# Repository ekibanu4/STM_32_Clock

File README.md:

# STM32 Binary Clock Lab

This repository is a development sandbox for a binary clock built around
different STM32 microcontrollers and peripheral combinations. It contains the
current clock firmware, earlier hardware ports, reusable device drivers, board
experiments, KiCad sources, and end-user documentation.

The project is intentionally broader than a single finished product: it is used
to test display concepts, sensors, RTC implementations, power management, alarm
behavior, and small-memory firmware optimizations on real hardware.

## MCU variants

- **STM32L010F4P6** - current primary target and the most complete low-power build.
- **STM32F030F4P6** - compact CubeMX/HAL port used during early hardware tests.
- **STM32F407G-DISC1** - original prototype and development platform.

The default CMake configuration currently builds the STM32L010F4P6 firmware.
Board-specific notes and wiring are kept under [`Core/Src/boards`](Core/Src/boards).

## Hardware and drivers

The repository includes implementations or experiments for:

- a 16-LED binary display driven by chained 74HC595 shift registers;
- a 128x32 OLED display;
- an internal STM32 RTC clocked from a 32.768 kHz LSE crystal;
- the external DS1302 RTC used by earlier board versions;
- AHT10 and DHT11 temperature/humidity sensors;
- BH1750 and analog LDR light sensing with automatic display brightness;
- an ADC resistor ladder for five control buttons;
- active-buzzer alarm output and three persistent alarm slots;
- PIR motion detection, idle display shutdown, battery measurement, and standby
  power handling.

Separate branches also preserve display and peripheral experiments such as the
MAX721x 8x8 LED matrix version.

## Firmware layout

- `Core/Src/app` - clock behavior, alarms, display rendering, environment data,
  automatic modes, and user-interface state.
- `Core/Src/boards` - MCU/board-specific GPIO and peripheral implementations.
- `Core/Src/drivers` - reusable drivers for buttons, buzzer, DHT11, DS1302,
  light sensing, and shift registers.
- `Drivers` - STM32 CMSIS and HAL sources.
- `docs` - user guide, technical reference, diagrams, and promotional assets.
- `Clocl i2C l0 16 -2 595` - KiCad schematic and PCB sources for the current
  STM32L010-based hardware.

## Build

The current target requires CMake, Ninja, and the GNU Arm Embedded toolchain.

```bash
cmake --preset Release
cmake --build --preset Release
```

Debug and Release presets place their output under `build/`.

## Documentation

- [User manual](docs/clock-plus-user-manual.md)
- [Technical reference](docs/clock-plus-technical-reference.md)
- [STM32L010 board notes](Core/Src/boards/l010f4p6/README.md)
- [STM32F030 board notes](Core/Src/boards/f030f4p6/README.md)
- [STM32F407 board notes](Core/Src/boards/f407_disc1/README.md)

This is an experimental hardware/firmware repository. Verify the selected board
configuration, supply voltage, pin mapping, and programming setup before using
it on assembled hardware.

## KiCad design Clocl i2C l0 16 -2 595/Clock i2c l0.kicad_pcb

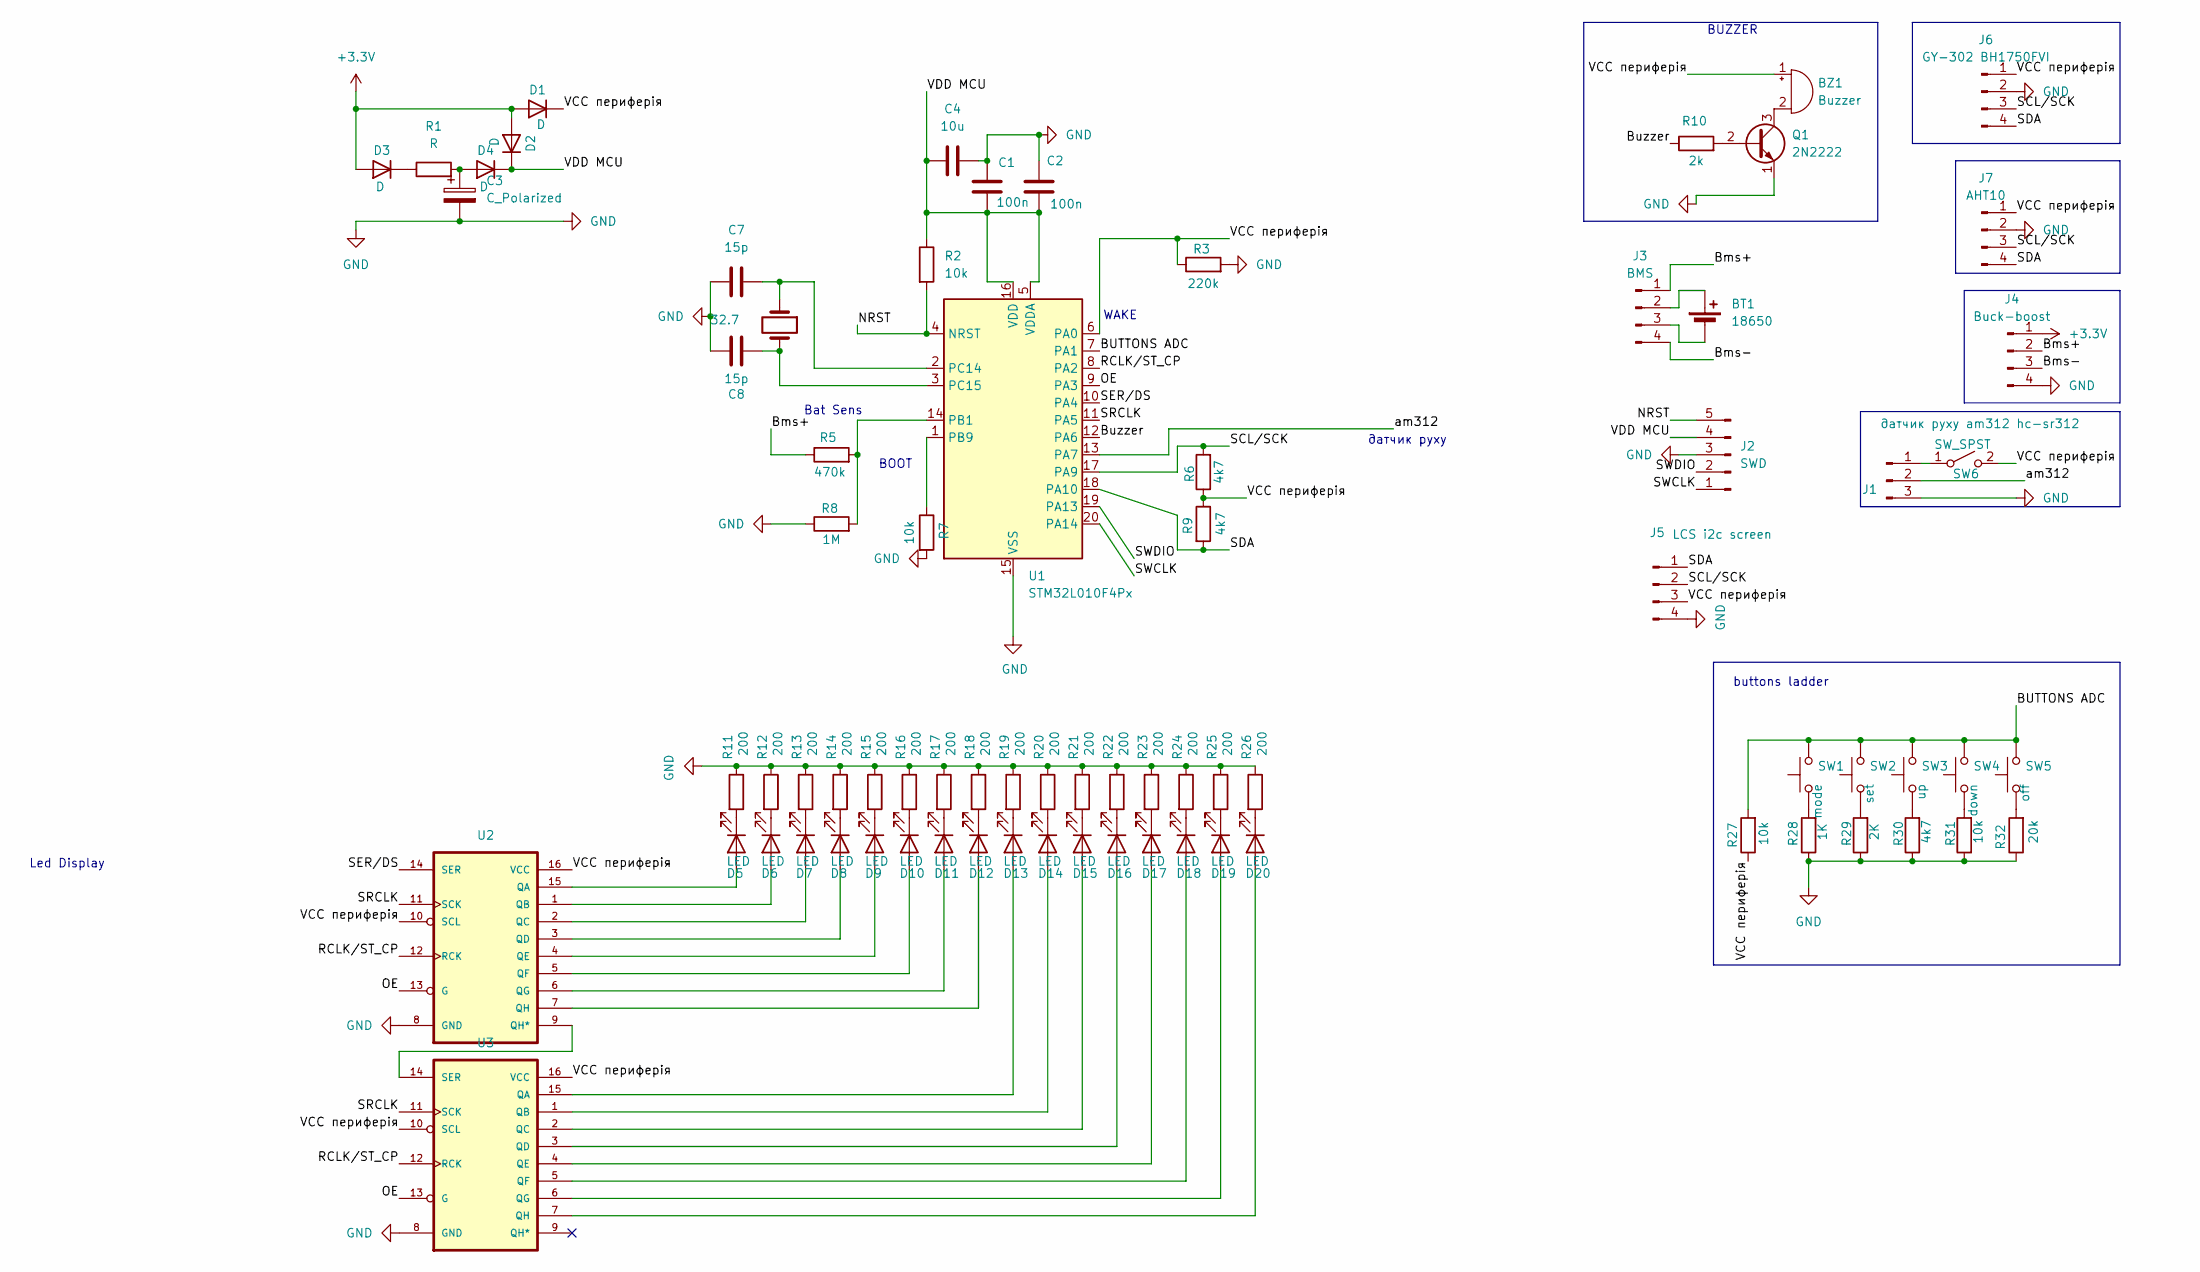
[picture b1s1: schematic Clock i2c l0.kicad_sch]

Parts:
BT1: 18650; BatteryHolder_MPD_BH-18650-PC
BZ1: Buzzer; Buzzer_12x9.5RM7.6
C1, C2: 100n; C_0805_2012Metric_Pad1.18x1.45mm_HandSolder
C3: C_Polarized; CP_Radial_D10.0mm_P5.00mm_P7.50mm
C4: 10u; C_0805_2012Metric_Pad1.18x1.45mm_HandSolder
C7, C8: 15p; C_0805_2012Metric_Pad1.18x1.45mm_HandSolder
D1, D2, D3, D4: D; D_0805_2012Metric_Pad1.15x1.40mm_HandSolder
D5, D6, D7, D8, D9, D10, D11, D12, D13, D14, D15, D16, D17, D18, D19, D20: LED; LED_D3.0mm
J1: датчик руху am312 hc-sr312; PinHeader_1x03_P2.54mm_Vertical
J2: SWD; PinHeader_1x05_P2.54mm_Vertical
J3: BMS; PinHeader_1x04_P2.54mm_Vertical
J4: Buck-boost; PinHeader_1x04_P2.54mm_Vertical
J5: LCS i2c screen; PinHeader_1x04_P2.54mm_Vertical
J6: GY-302 BH1750FVI; PinHeader_1x04_P2.54mm_Vertical
J7: AHT10; PinHeader_1x04_P2.54mm_Vertical
Q1: 2N2222; TO-92
R1: R; R_0805_2012Metric_Pad1.20x1.40mm_HandSolder
R2, R7, R27, R31: 10k; R_0805_2012Metric_Pad1.20x1.40mm_HandSolder
R3: 220k; R_0805_2012Metric_Pad1.20x1.40mm_HandSolder
R5: 470k; R_0805_2012Metric_Pad1.20x1.40mm_HandSolder
R6, R9, R30: 4k7; R_0805_2012Metric_Pad1.20x1.40mm_HandSolder
R8: 1M; R_0805_2012Metric_Pad1.20x1.40mm_HandSolder
R10: 2k; R_0805_2012Metric_Pad1.20x1.40mm_HandSolder
R11, R12, R13, R14, R15, R16, R17, R18, R19, R20, R21, R22, R23, R24, R25, R26: 200; R_0805_2012Metric_Pad1.20x1.40mm_HandSolder
R28: 1K; R_0805_2012Metric_Pad1.20x1.40mm_HandSolder
R29: 2K; R_0805_2012Metric_Pad1.20x1.40mm_HandSolder
R32: 20k; R_0805_2012Metric_Pad1.20x1.40mm_HandSolder
SW1: mode; SW_Push_1P1T_NO_CK_PTS125Sx73PSMTR
SW2: set; SW_Push_1P1T_NO_CK_PTS125Sx73PSMTR
SW3: up; SW_Push_1P1T_NO_CK_PTS125Sx73PSMTR
SW4: down; SW_Push_1P1T_NO_CK_PTS125Sx73PSMTR
SW5: off; SW_Push_1P1T_NO_CK_PTS125Sx73PSMTR
SW6: SW_SPST; PinHeader_1x02_P2.54mm_Vertical_SMD_Pin1Left
U1: STM32L010F4Px; TSSOP-20_4.4x6.5mm_P0.65mm
U2, U3: 74HC595N-DIP16; SOIC-16_3.9x9.9mm_P1.27mm; MPN 74HC595N
Y1: 32.7; Crystal_SMD_3215-2Pin_3.2x1.5mm

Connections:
+3.3V: D1.2 (A), D2.2 (A), D3.2 (A), J4.1
/BUTTONS ADC: R27.2, SW1.2, SW2.2, SW3.2, SW4.2, SW5.2, U1.7 (PA1)
/Bms+: J3.1, J4.2, R5.1
/Bms-: J3.4, J4.3
/Buzzer: R10.1, U1.12 (PA6)
/NRST: J2.5, R2.2, U1.4 (NRST)
/OE: U1.9 (PA3), U2.13 (G), U3.13 (G)
/RCLK/ST_CP: U1.8 (PA2), U2.12 (RCK), U3.12 (RCK)
/SCL/SCK: J5.2, J6.3, J7.3, R6.2, U1.17 (PA9)
/SDA: J5.1, J6.4, J7.4, R9.2, U1.18 (PA10)
/SER/DS: U1.10 (PA4), U2.14 (SER)
/SRCLK: U1.11 (PA5), U2.11 (SCK), U3.11 (SCK)
/SWCLK: J2.1, U1.20 (PA14)
/SWDIO: J2.2, U1.19 (PA13)
/VCC периферія: BZ1.1 (+), D1.1 (K), J5.3, J6.1, J7.1, R3.1, R6.1, R9.1, R27.1, SW6.2 (B), U1.6 (PA0), U2.10 (SCL), U2.16 (VCC), U3.10 (SCL), U3.16 (VCC)
/VDD MCU: C1.2, C2.2, C4.1, D2.1 (K), D4.1 (K), J2.4, R2.1, U1.5 (VDDA), U1.16 (VDD)
/am312: J1.2, U1.13 (PA7)
GND: C1.1, C2.1, C3.2, C4.2, C7.1, C8.1, J1.3, J2.3, J4.4, J5.4, J6.2, J7.2, Q1.1 (E), R3.2, R7.2, R8.1, R11.1, R12.1, R13.1, R14.1, R15.1, R16.1, R17.1, R18.1, R19.1, R20.1, R21.1, R22.1, R23.1, R24.1, R25.1, R26.1, R28.1, R29.1, R30.1, R31.1, R32.1, U1.15 (VSS), U2.8 (GND), U3.8 (GND)
unnamed: BT1.1 (+), J3.2
unnamed: BT1.2 (-), J3.3
unnamed: BZ1.2 (-), Q1.3 (C)
unnamed: D3.1 (K), R1.1
unnamed: C3.1, D4.2 (A), R1.2
unnamed: D5.2 (A), U2.15 (QA)
unnamed: D5.1 (K), R11.2
unnamed: D6.2 (A), U2.1 (QB)
unnamed: D6.1 (K), R12.2
unnamed: D7.2 (A), U2.2 (QC)
unnamed: D7.1 (K), R13.2
unnamed: D8.2 (A), U2.3 (QD)
unnamed: D8.1 (K), R14.2
unnamed: D9.2 (A), U2.4 (QE)
unnamed: D9.1 (K), R15.2
unnamed: D10.2 (A), U2.5 (QF)
unnamed: D10.1 (K), R16.2
unnamed: D11.2 (A), U2.6 (QG)
unnamed: D11.1 (K), R17.2
unnamed: D12.2 (A), U2.7 (QH)
unnamed: D12.1 (K), R18.2
unnamed: D13.2 (A), U3.15 (QA)
unnamed: D13.1 (K), R19.2
unnamed: D14.2 (A), U3.1 (QB)
unnamed: D14.1 (K), R20.2
unnamed: D15.2 (A), U3.2 (QC)
unnamed: D15.1 (K), R21.2
unnamed: D16.2 (A), U3.3 (QD)
unnamed: D16.1 (K), R22.2
unnamed: D17.2 (A), U3.4 (QE)
unnamed: D17.1 (K), R23.2
unnamed: D18.2 (A), U3.5 (QF)
unnamed: D18.1 (K), R24.2
unnamed: D19.2 (A), U3.6 (QG)
unnamed: D19.1 (K), R25.2
unnamed: D20.2 (A), U3.7 (QH)
unnamed: D20.1 (K), R26.2
unnamed: J1.1, SW6.1 (A)
unnamed: Q1.2 (B), R10.2
unnamed: R28.2, SW1.1
unnamed: R29.2, SW2.1
unnamed: R30.2, SW3.1
unnamed: R31.2, SW4.1
unnamed: R32.2, SW5.1
unnamed: R5.2, R8.2, U1.14 (PB1)
unnamed: R7.1, U1.1 (PB9)
unnamed: C7.2, U1.2 (PC14), Y1.1
unnamed: C8.2, U1.3 (PC15), Y1.2
unnamed: U2.9 (QH*), U3.14 (SER)

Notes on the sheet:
датчик руху
WAKE
Bat Sens
buttons ladder
BOOT
Led Display
BUZZER

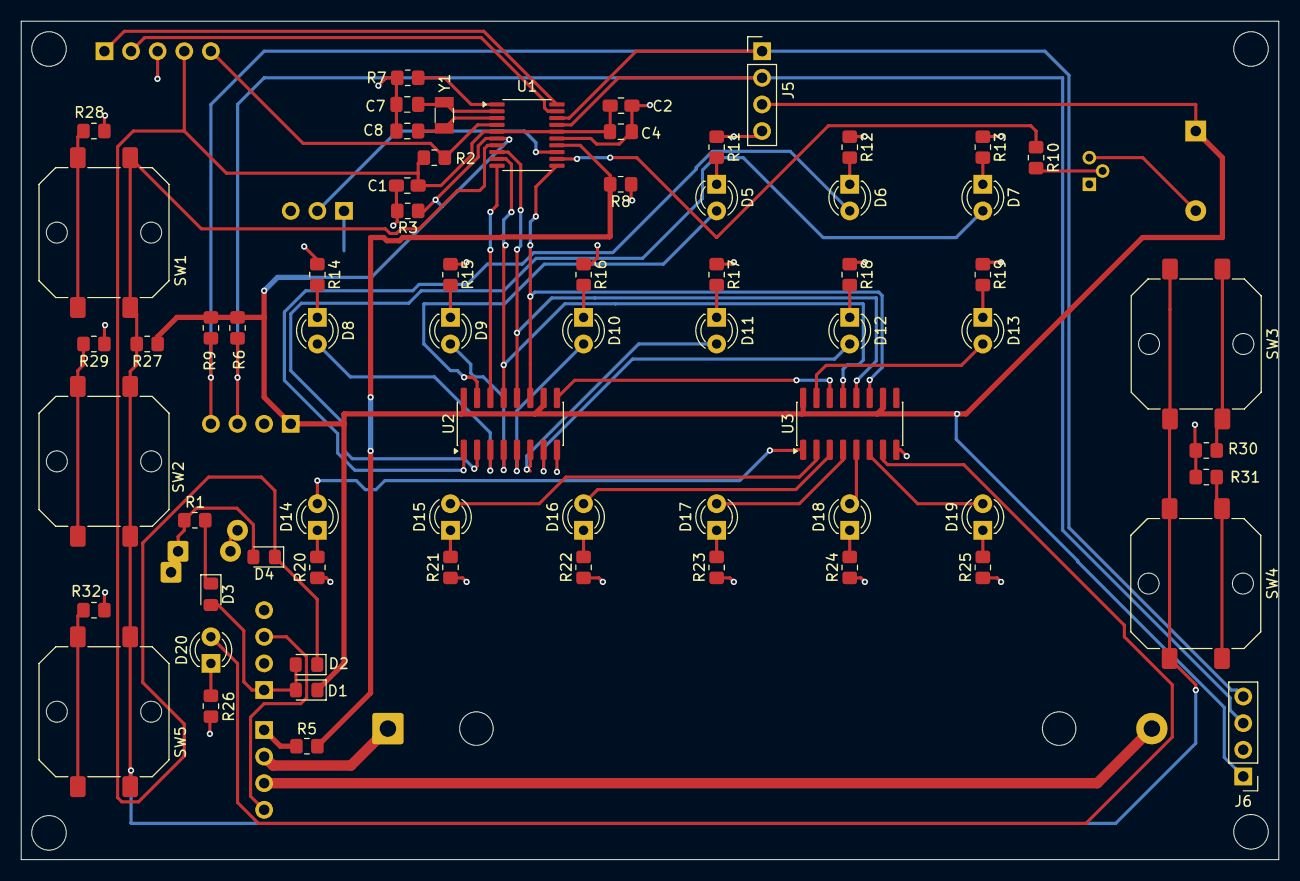
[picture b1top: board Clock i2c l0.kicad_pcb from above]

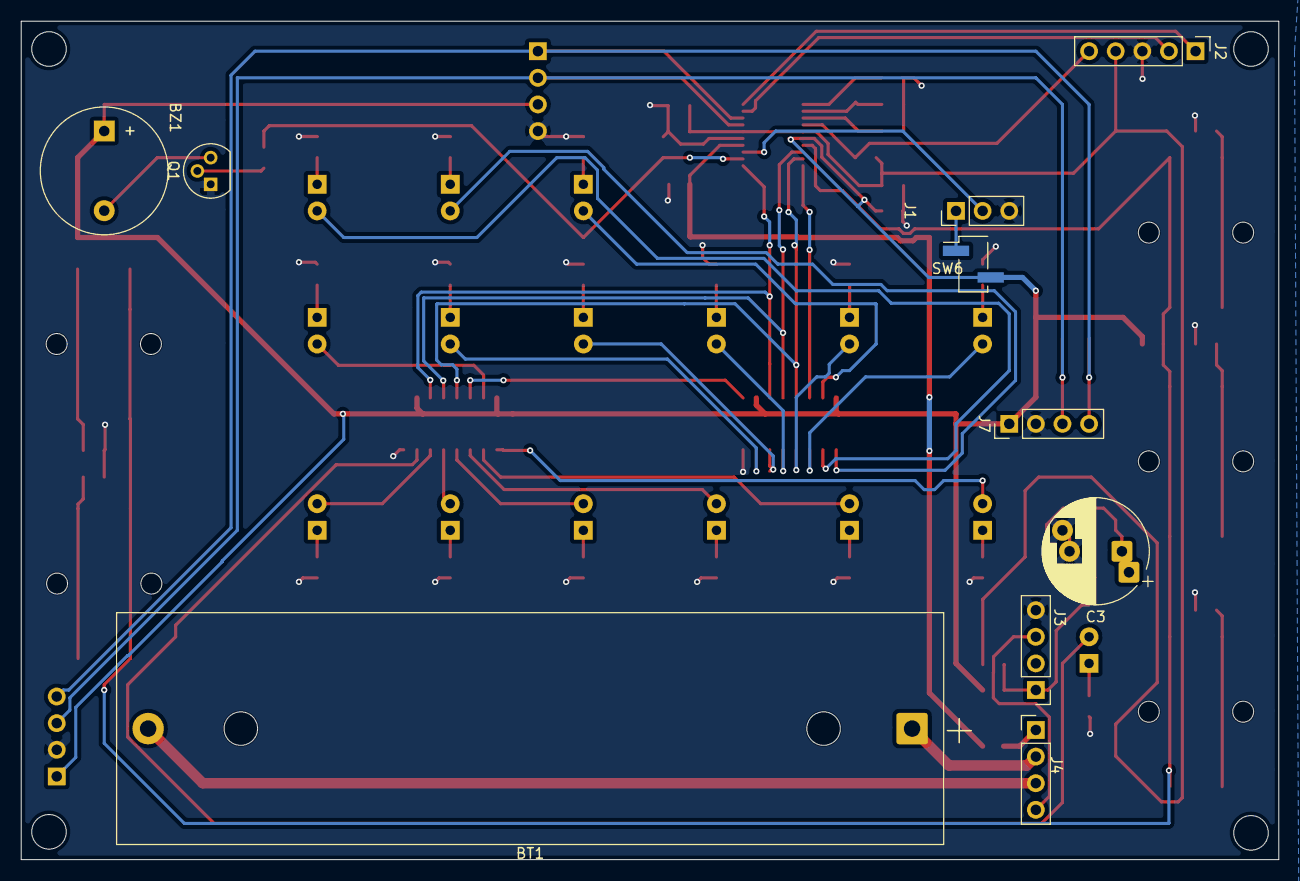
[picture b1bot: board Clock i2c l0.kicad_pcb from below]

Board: 2 copper layers, 120.0 x 80.0 mm, 77 parts (10 on the bottom side), 67 nets.

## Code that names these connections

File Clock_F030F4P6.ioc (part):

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Mcu.Name=STM32F030F4Px
Mcu.Package=TSSOP20
Mcu.UserName=STM32F030F4Px
PA0.Mode=IN0
PA0.Signal=ADC_IN0
PA1.Mode=IN1
PA1.Signal=ADC_IN1
PA10.Signal=GPIO_Output
PA13.Mode=Serial_Wire
PA13.Signal=SYS_SWDIO
PA14.Mode=Serial_Wire
PA14.Signal=SYS_SWCLK
PA2.Signal=GPIO_Output
PA3.Signal=GPIO_Output
PA5.Signal=GPIO_Output
PA6.Signal=S_TIM3_CH1
PA7.Signal=GPIO_Output
PA9.Signal=GPIO_Input
PB1.Signal=GPIO_Output
PF1-OSC_OUT.Signal=GPIO_Input
board=custom

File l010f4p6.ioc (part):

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Mcu.Name=STM32L010F4Px
Mcu.Package=TSSOP20
Mcu.UserName=STM32L010F4Px
PA0-CK_IN.Mode=SYS_WakeUp0
PA0-CK_IN.Signal=SYS_WKUP1
PA1.Mode=IN1
PA1.Signal=ADC_IN1
PA13.Mode=Serial_Wire
PA13.Signal=SYS_SWDIO
PA14.Mode=Serial_Wire
PA14.Signal=SYS_SWCLK
PA2.Signal=GPIO_Output
PA3.Signal=GPIO_Output
PA4.Signal=GPIO_Output
PA5.Signal=S_TIM2_CH1
PB1.Mode=IN9
PB1.Signal=ADC_IN9
PC14-OSC32_IN.Mode=LSE-External-Oscillator
PC14-OSC32_IN.Signal=RCC_OSC32_IN
PC15-OSC32_OUT.Mode=LSE-External-Oscillator
PC15-OSC32_OUT.Signal=RCC_OSC32_OUT
RCC.HSE_VALUE=8000000
RCC.SYSCLKFreq_VALUE=2097000
board=custom

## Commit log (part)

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2026-06-23 Phase 1 STM32F407 binary clock prototype
2026-06-24 Refactor hardware into board packages and drivers
2026-06-24 Refactor app modules and document F407 pinout
